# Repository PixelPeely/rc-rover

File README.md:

# rc-rover
Arduino-powered rc rover with live video feed

# Controller
## Custom circuit board:
The Controller PCB is responsible for charging a LiCD battery, as well as powering the screen board, which is an independent unit. The board contains through holes for the NRF24L01+ module, along with 4 LMS-5161 common anode 7 segment displays that are controlled by 4 74HC595 8-bit shift registers, all of which are controlled by an arduino nano every and powered by the LiCD battery.
Schematic:

Footprint:

3D Render:

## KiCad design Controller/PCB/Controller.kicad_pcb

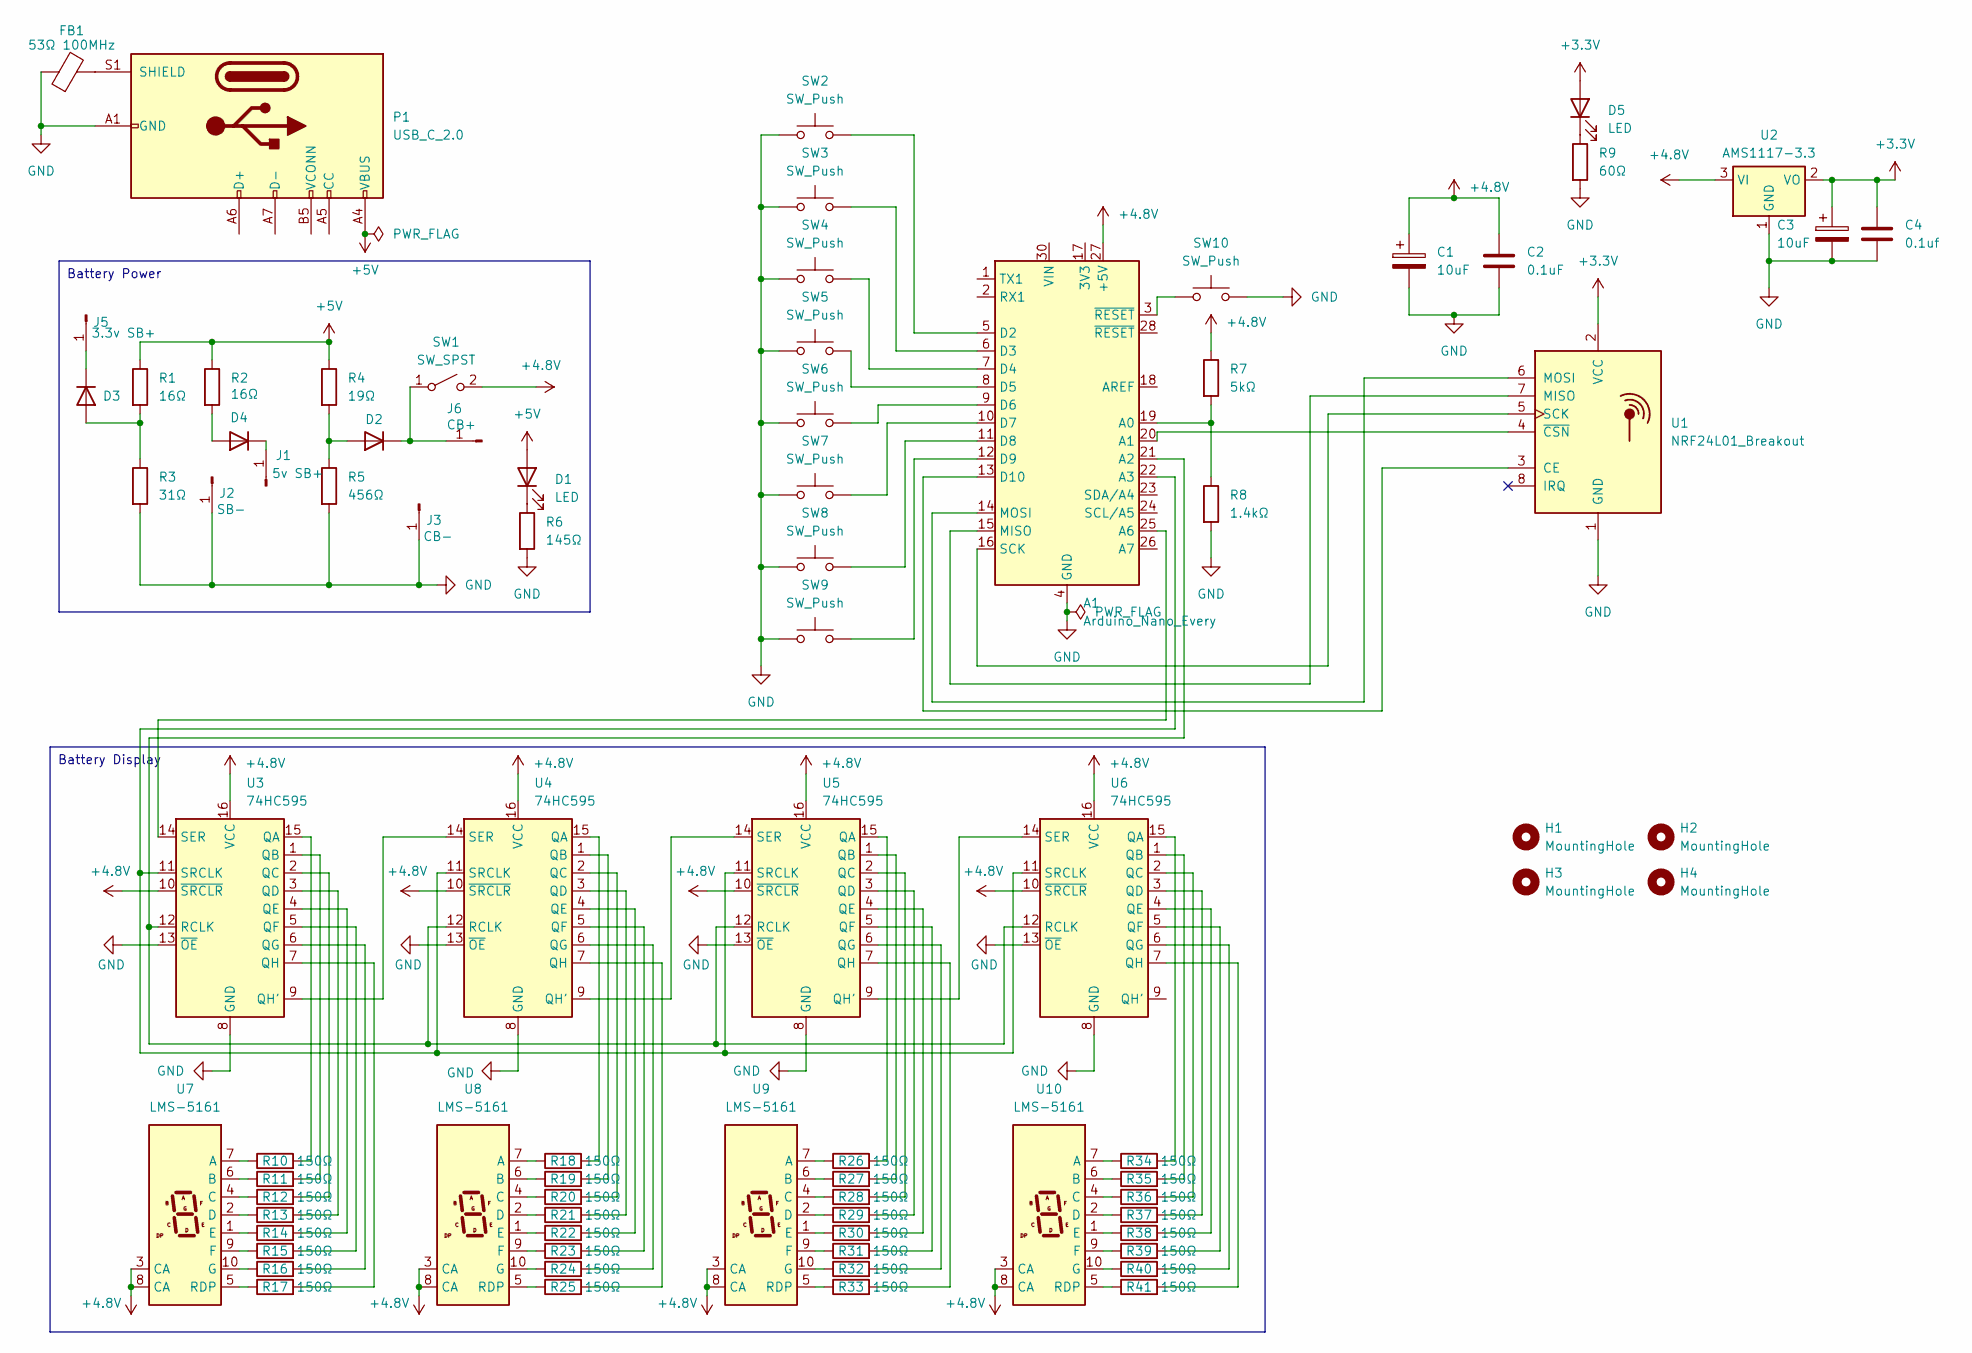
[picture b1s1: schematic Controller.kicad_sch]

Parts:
A1: Arduino_Nano_Every; Arduino_Nano
C1, C3: 10uF; CP_Radial_D5.0mm_P2.00mm
C2: 0.1uF; C_Rect_L7.2mm_W2.5mm_P5.00mm_FKS2_FKP2_MKS2_MKP2
C4: 0.1uf; C_Rect_L7.2mm_W2.5mm_P5.00mm_FKS2_FKP2_MKS2_MKP2
D1, D5: LED; D_A-405_P2.54mm_Vertical_AnodeUp
D2, D3, D4: D; D_A-405_P12.70mm_Horizontal
FB1: 53Ω 100MHz; C_Rect_L7.2mm_W2.5mm_P5.00mm_FKS2_FKP2_MKS2_MKP2
H1, H2, H3, H4: MountingHole; MountingHole_4.3mm_M4
J1: 5v SB+; SolderWire-0.5sqmm_1x01_D0.9mm_OD2.1mm
J2: SB-; SolderWire-0.5sqmm_1x01_D0.9mm_OD2.1mm
J3: CB-; SolderWire-0.5sqmm_1x01_D0.9mm_OD2.1mm
J5: 3.3v SB+; SolderWire-0.5sqmm_1x01_D0.9mm_OD2.1mm
J6: CB+; SolderWire-0.5sqmm_1x01_D0.9mm_OD2.1mm
P1: USB_C_2.0; USB_C_Receptacle_GCT_USB4125-xx-x_6P_TopMnt_Horizontal
R1, R2: 16Ω; R_Axial_DIN0207_L6.3mm_D2.5mm_P10.16mm_Horizontal
R3: 31Ω; R_Axial_DIN0207_L6.3mm_D2.5mm_P10.16mm_Horizontal
R4: 19Ω; R_Axial_DIN0207_L6.3mm_D2.5mm_P10.16mm_Horizontal
R5: 456Ω; R_Axial_DIN0207_L6.3mm_D2.5mm_P10.16mm_Horizontal
R6: 145Ω; R_Axial_DIN0207_L6.3mm_D2.5mm_P10.16mm_Horizontal
R7: 5kΩ; R_Axial_DIN0207_L6.3mm_D2.5mm_P10.16mm_Horizontal
R8: 1.4kΩ; R_Axial_DIN0207_L6.3mm_D2.5mm_P10.16mm_Horizontal
R9: 60Ω; R_Axial_DIN0207_L6.3mm_D2.5mm_P10.16mm_Horizontal
R10, R11, R12, R13, R14, R15, R16, R17, R18, R19, R20, R21, R22, R23, R24, R25, R26, R27, R28, R29, R30, R31, R32, R33, R34, R35, R36, R37, R38, R39, R40, R41: 150Ω; R_Axial_DIN0207_L6.3mm_D2.5mm_P10.16mm_Horizontal
SW1: SW_SPST; SW_DIP_SPSTx01_Slide_9.78x4.72mm_W7.62mm_P2.54mm
SW2, SW3, SW4, SW5, SW6, SW7, SW8, SW9, SW10: SW_Push; SW_PUSH_Singular_6mm
U1: NRF24L01_Breakout; nRF24L01_Antenna
U2: AMS1117-3.3; SOT-223-3_TabPin2
U3, U4, U5, U6: 74HC595; DIP-16_W7.62mm_Socket
U7, U8, U9, U10: LMS-5161

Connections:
+3.3V: C3.1, C4.1, D5.2 (A), U1.2 (VCC), U2.2 (VO)
+4.8V: A1.27 (+5V), C1.1, C2.1, R7.1, SW1.2 (B), U2.3 (VI), U3.10 (~SRCLR), U3.16 (VCC), U4.10 (~SRCLR), U4.16 (VCC), U5.10 (~SRCLR), U5.16 (VCC), U6.10 (~SRCLR), U6.16 (VCC), U7.3 (CA), U7.8 (CA), U8.3 (CA), U8.8 (CA), U9.3 (CA), U9.8 (CA), U10.3 (CA), U10.8 (CA)
+5V: D1.2 (A), P1.A4 (VBUS), P1.A9 (VBUS), P1.B4 (VBUS), P1.B9 (VBUS), R1.1, R2.1, R4.1
GND: A1.4 (GND), A1.29 (GND), C1.2, C2.2, C3.2, C4.2, FB1.1, J2.1, J3.1, P1.A1 (GND), P1.A12 (GND), P1.B1 (GND), P1.B12 (GND), R3.2, R5.2, R6.2, R8.2, R9.2, SW2.1, SW3.1, SW4.1, SW5.1, SW6.1, SW7.1, SW8.1, SW9.1, SW10.2, U1.1 (GND), U2.1 (GND), U3.8 (GND), U3.13 (~OE), U4.8 (GND), U4.13 (~OE), U5.8 (GND), U5.13 (~OE), U6.8 (GND), U6.13 (~OE)
unnamed: A1.19 (A0), R7.2, R8.1
unnamed: A1.20 (A1), U1.4 (~CSN)
unnamed: A1.21 (A2), U3.12 (RCLK), U4.12 (RCLK), U5.12 (RCLK), U6.12 (RCLK)
unnamed: A1.22 (A3), U3.11 (SRCLK), U4.11 (SRCLK), U5.11 (SRCLK), U6.11 (SRCLK)
unnamed: A1.25 (A6), U3.14 (SER)
unnamed: A1.5 (D2), SW2.2
unnamed: A1.6 (D3), SW3.2
unnamed: A1.7 (D4), SW4.2
unnamed: A1.8 (D5), SW5.2
unnamed: A1.9 (D6), SW6.2
unnamed: A1.10 (D7), SW7.2
unnamed: A1.11 (D8), SW8.2
unnamed: A1.12 (D9), SW9.2
unnamed: A1.13 (D10), U1.3 (CE)
unnamed: A1.15 (MISO), U1.7 (MISO)
unnamed: A1.14 (MOSI), U1.6 (MOSI)
unnamed: A1.16 (SCK), U1.5 (SCK)
unnamed: A1.3 (~RESET), SW10.1
unnamed: D1.1 (K), R6.1
unnamed: D2.2 (A), R4.2, R5.1
unnamed: D2.1 (K), J6.1, SW1.1 (A)
unnamed: D3.2 (A), R1.2, R3.1
unnamed: D3.1 (K), J5.1
unnamed: D4.2 (A), R2.2
unnamed: D4.1 (K), J1.1
unnamed: D5.1 (K), R9.1
unnamed: FB1.2, P1.S1 (SHIELD)
unnamed: R10.2, U3.15 (QA)
unnamed: R11.2, U3.1 (QB)
unnamed: R12.2, U3.2 (QC)
unnamed: R13.2, U3.3 (QD)
unnamed: R14.2, U3.4 (QE)
unnamed: R15.2, U3.5 (QF)
unnamed: R16.2, U3.6 (QG)
unnamed: U3.9 (QH'), U4.14 (SER)
unnamed: R17.2, U3.7 (QH)
unnamed: R18.2, U4.15 (QA)
unnamed: R19.2, U4.1 (QB)
unnamed: R20.2, U4.2 (QC)
unnamed: R21.2, U4.3 (QD)
unnamed: R22.2, U4.4 (QE)
unnamed: R23.2, U4.5 (QF)
unnamed: R24.2, U4.6 (QG)
unnamed: U4.9 (QH'), U5.14 (SER)
unnamed: R25.2, U4.7 (QH)
unnamed: R26.2, U5.15 (QA)
unnamed: R27.2, U5.1 (QB)
unnamed: R28.2, U5.2 (QC)
unnamed: R29.2, U5.3 (QD)
unnamed: R30.2, U5.4 (QE)
unnamed: R31.2, U5.5 (QF)
unnamed: R32.2, U5.6 (QG)
unnamed: U5.9 (QH'), U6.14 (SER)
unnamed: R33.2, U5.7 (QH)
unnamed: R34.2, U6.15 (QA)
unnamed: R35.2, U6.1 (QB)
unnamed: R36.2, U6.2 (QC)
unnamed: R37.2, U6.3 (QD)
unnamed: R38.2, U6.4 (QE)
unnamed: R39.2, U6.5 (QF)
unnamed: R40.2, U6.6 (QG)
unnamed: R41.2, U6.7 (QH)
unnamed: R10.1, U7.7 (A)
unnamed: R11.1, U7.6 (B)
unnamed: R12.1, U7.4 (C)
unnamed: R13.1, U7.2 (D)
unnamed: R14.1, U7.1 (E)
unnamed: R15.1, U7.9 (F)
unnamed: R16.1, U7.10 (G)
unnamed: R17.1, U7.5 (RDP)
unnamed: R18.1, U8.7 (A)
unnamed: R19.1, U8.6 (B)
unnamed: R20.1, U8.4 (C)
unnamed: R21.1, U8.2 (D)
unnamed: R22.1, U8.1 (E)
unnamed: R23.1, U8.9 (F)
unnamed: R24.1, U8.10 (G)
unnamed: R25.1, U8.5 (RDP)
unnamed: R26.1, U9.7 (A)
unnamed: R27.1, U9.6 (B)
unnamed: R28.1, U9.4 (C)
unnamed: R29.1, U9.2 (D)
unnamed: R30.1, U9.1 (E)
unnamed: R31.1, U9.9 (F)
unnamed: R32.1, U9.10 (G)
unnamed: R33.1, U9.5 (RDP)
unnamed: R34.1, U10.7 (A)
unnamed: R35.1, U10.6 (B)
unnamed: R36.1, U10.4 (C)
unnamed: R37.1, U10.2 (D)
unnamed: R38.1, U10.1 (E)
unnamed: R39.1, U10.9 (F)
unnamed: R40.1, U10.10 (G)
unnamed: R41.1, U10.5 (RDP)

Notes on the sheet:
Battery Display
Battery Power

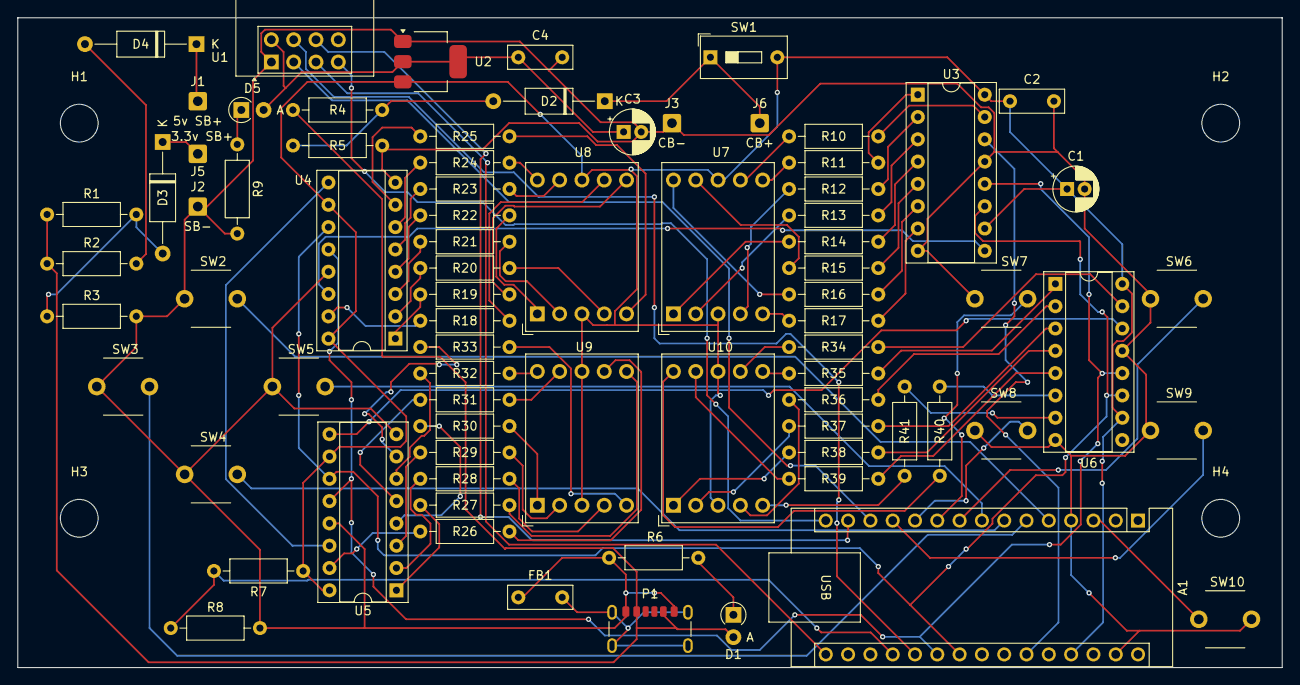
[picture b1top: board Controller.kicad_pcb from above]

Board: 2 copper layers, 144.0 x 74.0 mm, 82 parts (0 on the bottom side), 98 nets.

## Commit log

2024-07-14 Back Silkscreen Label
2024-07-14 Reorganize
2024-07-14 Add README
2025-01-07 Upload controller code
